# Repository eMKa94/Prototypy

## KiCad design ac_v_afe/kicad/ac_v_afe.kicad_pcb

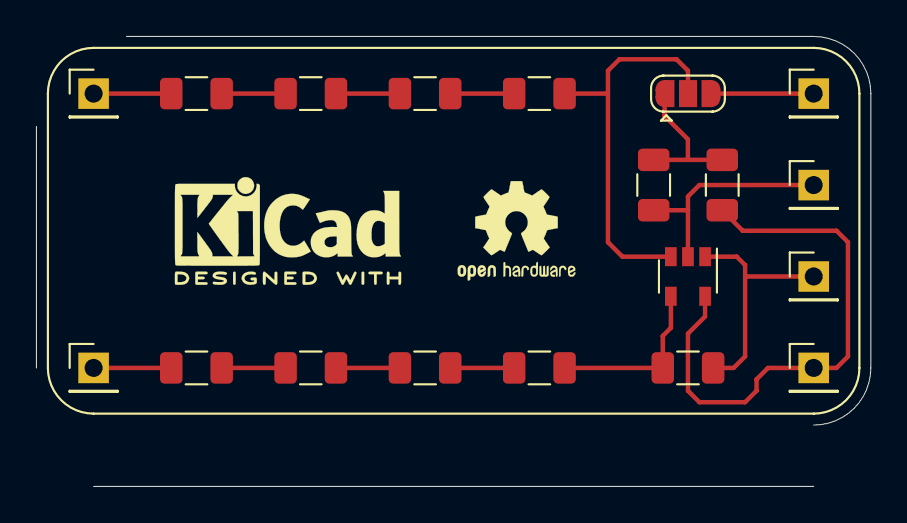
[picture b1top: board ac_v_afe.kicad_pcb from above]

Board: 2 copper layers, 46.4 x 25.0 mm, 19 parts (0 on the bottom side), 15 nets.

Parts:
J1: AC L; PinHeader_1x01_P2.54mm_Vertical
J2: AC N; PinHeader_1x01_P2.54mm_Vertical
J3: V_ref; PinHeader_1x01_P2.54mm_Vertical
J4: VDDA; PinHeader_1x01_P2.54mm_Vertical
J5: SIGNAL; PinHeader_1x01_P2.54mm_Vertical
J6: GNDA; PinHeader_1x01_P2.54mm_Vertical
JP1: Jumper_3_Bridged12; SolderJumper-3_P1.3mm_Open_RoundedPad1.0x1.5mm
R1, R2, R3, R4, R5, R6, R7, R8, R9, R10, R11: R; R_1206_3216Metric
U1: MCP6021T; SOT-23-5

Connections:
/AC_V_L: J1.1, R1.2
/AC_V_N: J2.1, R2.2
/GNDA: J6.1, R8.1, U1.2
/OUT_SIG: J5.1, R11.1, U1.1
/Reference_voltage: JP1.2, R9.1, U1.3
/VDDA: J4.1, R7.2, U1.5
/V_div: JP1.1, R7.1, R8.2
/ext_ref: J3.1, JP1.3
unnamed: R1.1, R3.2
unnamed: R2.1, R4.2
unnamed: R3.1, R5.2
unnamed: R4.1, R6.2
unnamed: R5.1, R9.2
unnamed: R10.1, R11.2, U1.4
unnamed: R6.1, R10.2
